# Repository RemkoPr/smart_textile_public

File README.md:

# Smart Textile [public repo]

This repo contains a manufaturing guide of and code for the smart textile featured in the MDPI paper [Modular Piezoresistive Smart Textile for State Estimation of Cloths](https://doi.org/10.3390/s22010222). Data obtained during the experiments outlined in this paper can be found on [Zenodo](https://doi.org/10.5281/zenodo.5718426).

Further information in README's in the subfolders.

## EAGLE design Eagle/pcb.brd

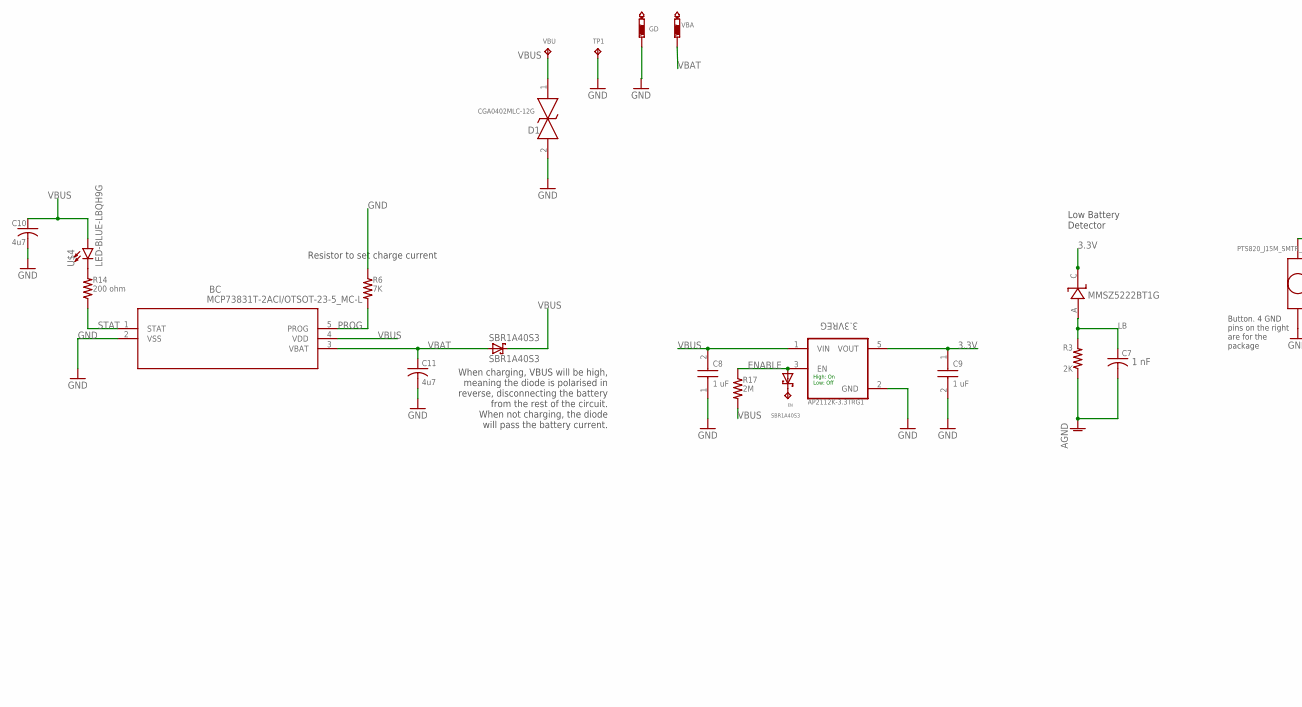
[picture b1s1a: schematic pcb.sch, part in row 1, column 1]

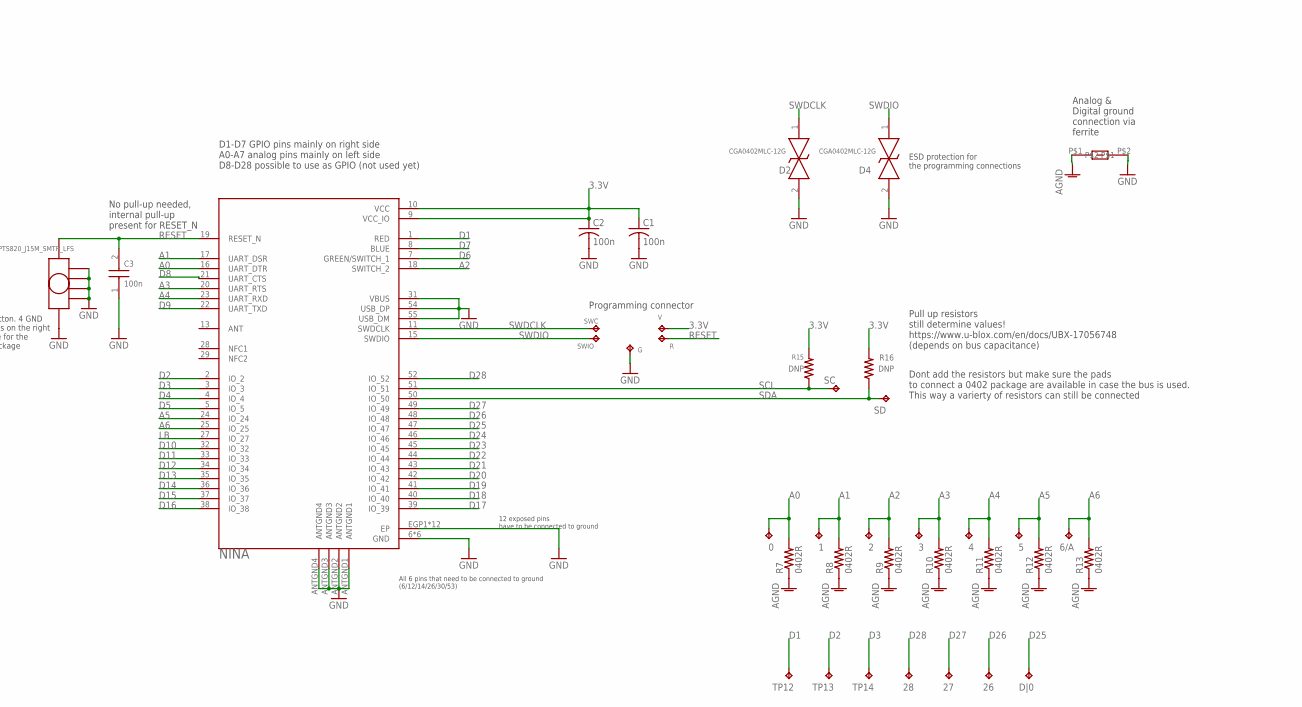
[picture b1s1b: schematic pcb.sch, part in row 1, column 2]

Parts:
0, 1, 2, 3, 4, 5, 6/A, 26, 27, 28: CUSTOM_HOLE1; CUSTOM_HOLE
3.3VREG: AP2112K-3.3TRG1; SOT95P285X140-5N
BC: MCP73831T-2ACI/OTSOT-23-5_MC-L; SOT-23-5_MC-L
BUTTON: PTS820_J15M_SMTR_LFS; PTS820_J15
C1, C2: 100n; C0402
C3: 100n; CAPC1005X33N
C7: 1 nF; C0402
C8, C9: 1 uF; CAPC1005X33N
C10, C11: 4u7; C0402
D1, D2, D4: CGA0402MLC-12G; CGA0402MLC12G
D|0: CUSTOM_HOLE1; CUSTOM_HOLE
EN: CUSTOM_HOLE1; CUSTOM_HOLE
G: TPB1,27; B1,27
GD: PTR1TP18R; TP18R
MMSZ5222BT1G: MMSZ5222BT1G; SOD−123
R: TPB1,27; B1,27
R3: 2K; RESC1005X40N
R6: 7K; RESC1005X40N
R7, R8, R9, R10, R11, R12, R13: 0402R; RESC1005X40N
R14: 200 ohm; RESC1005X40N
R15, R16: DNP; RESC1005X40N
R17: 2M; RESC1005X40N
SBR1A40S3: SBR1A40S3; SOD323
SC: CUSTOM_HOLE1; CUSTOM_HOLE
SD: CUSTOM_HOLE1; CUSTOM_HOLE
SWC: TPB1,27; B1,27
SWIO: TPB1,27; B1,27
TP1, TP12, TP13, TP14: CUSTOM_HOLE1; CUSTOM_HOLE
U1: NINA; XCVR_NINA-B306
U$2: SBR1A40S3; SOD323
U$4: LED-BLUE-LBQH9G; LBQH9G-0402
U$5: BLM18KG121WH1D; 0603
V: TPB1,27; B1,27
VBA: PTR1TP18R; TP18R
VBU: CUSTOM_HOLE1; CUSTOM_HOLE

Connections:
3.3V: 3.3VREG.5 (VOUT), C1.1, C2.1, C9.1, MMSZ5222BT1G.C, R15.2, R16.2, U1.9 (VCC_IO), U1.10 (VCC), V.TP
A0: 0.P$1, R7.2, U1.16 (UART_DTR)
A1: 1.P$1, R8.2, U1.17 (UART_DSR)
A2: 2.P$1, R9.2, U1.18 (SWITCH_2)
A3: 3.P$1, R10.2, U1.20 (UART_RTS)
A4: 4.P$1, R11.2, U1.23 (UART_RXD)
A5: 5.P$1, R12.2, U1.24 (IO_24)
A6: 6/A.P$1, R13.2, U1.25 (IO_25)
AGND: C7.2, R3.1, R7.1, R8.1, R9.1, R10.1, R11.1, R12.1, R13.1, U$5.P$1
D1: TP12.P$1, U1.1 (RED)
D2: TP13.P$1, U1.2 (IO_2)
D3: TP14.P$1, U1.3 (IO_3)
D4: U1.4 (IO_4)
D5: U1.5 (IO_5)
D6: U1.7 (GREEN/SWITCH_1)
D7: U1.8 (BLUE)
D8: U1.21 (UART_CTS)
D9: U1.22 (UART_TXD)
D10: U1.32 (IO_32)
D11: U1.33 (IO_33)
D12: U1.34 (IO_34)
D13: U1.35 (IO_35)
D14: U1.36 (IO_36)
D15: U1.37 (IO_37)
D16: U1.38 (IO_38)
D17: U1.39 (IO_39)
D18: U1.40 (IO_40)
D19: U1.41 (IO_41)
D20: U1.42 (IO_42)
D21: U1.43 (IO_43)
D22: U1.44 (IO_44)
D23: U1.45 (IO_45)
D24: U1.46 (IO_46)
D25: D|0.P$1, U1.47 (IO_47)
D26: 26.P$1, U1.48 (IO_48)
D27: 27.P$1, U1.49 (IO_49)
D28: 28.P$1, U1.52 (IO_52)
ENABLE: 3.3VREG.3 (EN), R17.1, U$2.A
GND: 3.3VREG.2 (GND), BC.2 (VSS), BUTTON.1, BUTTON.P$1, BUTTON.P$2, BUTTON.P$3, BUTTON.P$4, C1.2, C2.2, C3.1, C8.1, C9.2, C10.2, C11.2, D1.2, D2.2, D4.2, G.TP, GD.TP, R6.1, TP1.P$1, U1.6 (GND), U1.12 (GND), U1.14 (GND), U1.26 (GND), U1.30 (GND), U1.31 (VBUS), U1.53 (GND), U1.54 (USB_DP), U1.55 (USB_DM), U1.ANTGND1, U1.ANTGND2, U1.ANTGND3, U1.ANTGND4, U1.EGP1 (EP), U1.EGP2 (EP), U1.EGP3 (EP), U1.EGP4 (EP), U1.EGP5 (EP), U1.EGP6 (EP), U1.EGP7 (EP), U1.EGP8 (EP), U1.EGP9 (EP), U1.EGP10 (EP), U1.EGP11 (EP), U1.EGP12 (EP), U$5.P$2
LB: C7.1, MMSZ5222BT1G.A, R3.2, U1.27 (IO_27)
unnamed: R14.2, U$4.C
unnamed: EN.P$1, U$2.C
PROG: BC.5 (PROG), R6.2
RESET: BUTTON.2, C3.2, R.TP, U1.19 (RESET_N)
SCL: R15.1, SC.P$1, U1.51 (IO_51)
SDA: R16.1, SD.P$1, U1.50 (IO_50)
STAT: BC.1 (STAT), R14.1
SWDCLK: D2.1, SWC.TP, U1.11 (SWDCLK)
SWDIO: D4.1, SWIO.TP, U1.15 (SWDIO)
VBAT: BC.3 (VBAT), C11.1, SBR1A40S3.A, VBA.TP
VBUS: 3.3VREG.1 (VIN), BC.4 (VDD), C8.2, C10.1, D1.1, R17.2, SBR1A40S3.C, U$4.A, VBU.P$1

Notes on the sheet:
Low Battery Detector
High: On Low: Off
When charging, VBUS will be high, meaning the diode is polarised in reverse, disconnecting the battery from the rest of the circuit. When not charging, the diode will pass the battery current.
Resistor to set charge current
D1-D7 GPIO pins mainly on right side A0-A7 analog pins mainly on left side D8-D28 possible to use as GPIO (not used yet)
12 exposed pins have to be connected to ground
All 6 pins that need to be connected to ground (6/12/14/26/30/53)
Pull up resistors still determine values! https://www.u-blox.com/en/docs/UBX-17056748 (depends on bus capacitance)
Dont add the resistors but make sure the pads to connect a 0402 package are available in case the bus is used. This way a varierty of resistors can still be connected
No pull-up needed, internal pull-up present for RESET_N
Programming connector
Button. 4 GND pins on the right are for the package
ESD protection for the programming connections
Analog & Digital ground connection via ferrite

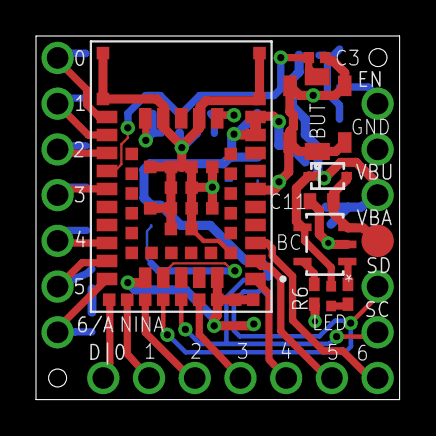
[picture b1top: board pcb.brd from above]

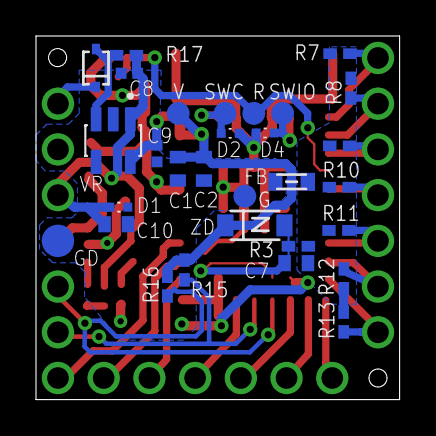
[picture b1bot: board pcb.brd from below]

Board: 2 copper layers, 20.2 x 20.2 mm, 59 parts (31 on the bottom side), 30 nets.

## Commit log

2022-01-03 Added Eagle library files

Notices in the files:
parts and their libraries:
SparkFun-LED: Licensing: Creative Commons ShareAlike 4.0 International - https://creativecommons.org/licenses/by-sa/4.0
